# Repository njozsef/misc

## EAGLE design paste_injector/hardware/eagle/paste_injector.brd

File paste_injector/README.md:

Arduino Motorized SMT Solder Paste Dispenser

Original design and code by Zapta
https://github.com/zapta/misc

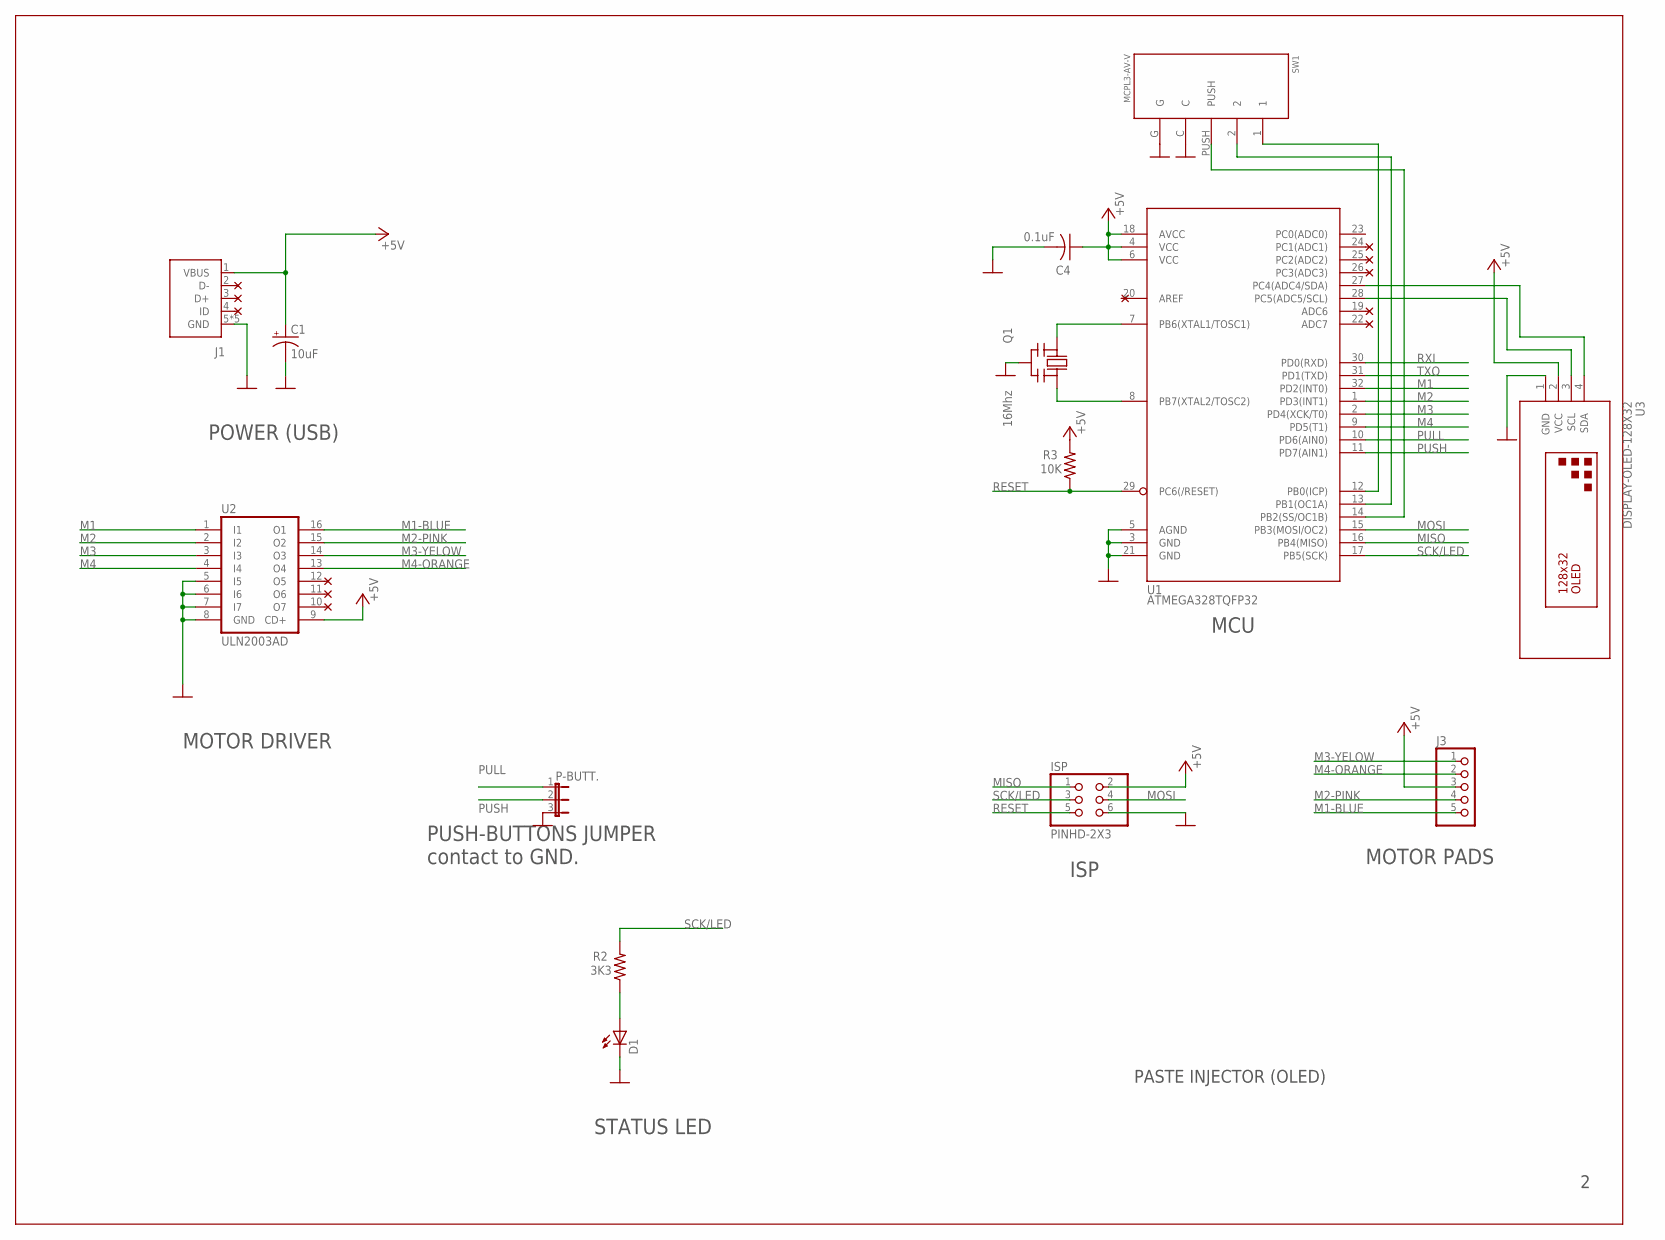
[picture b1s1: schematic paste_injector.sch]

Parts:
C1: 10uF; A/3216-18R
C4: 0.1uF; C0603
D1: LED; LED0603
ISP: PINHD-2X3; 2X03
J1: USB; USB-MICRO-ZX62RD-AB-5P8
J3: PINHD-1X5; 1X05
P-BUTT.: JP2E; JP2
Q1: 16Mhz; CSTCR-G
R2: 3K3; R0603
R3: 10K; R0603
SW1: MCPL3-AV-V; MCPL3-AC-V
U1: ATMEGA328TQFP32; TQFP32-08
U2: ULN2003AD; SO16
U3: DISPLAY-OLED-128X32

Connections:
+5V: C1.+, C4.1, ISP.2, J1.1 (VBUS), J3.3, R3.2, U1.4 (VCC), U1.6 (VCC), U1.18 (AVCC), U2.9 (CD+), U3.2 (VCC)
GND: C1.-, C4.2, D1.C, ISP.6, J1.5 (GND), J1.A (GND), J1.B (GND), J1.C (GND), J1.D (GND), P-BUTT..3, Q1.2 (GND), SW1.C, SW1.G, U1.3 (GND), U1.5 (AGND), U1.21 (GND), U2.5 (I5), U2.6 (I6), U2.7 (I7), U2.8 (GND), U3.1 (GND)
M1: U1.32 (PD2(INT0)), U2.1 (I1)
M1-BLUE: J3.5, U2.16 (O1)
M2: U1.1 (PD3(INT1)), U2.2 (I2)
M2-PINK: J3.4, U2.15 (O2)
M3: U1.2 (PD4(XCK/T0)), U2.3 (I3)
M3-YELOW: J3.1, U2.14 (O3)
M4: U1.9 (PD5(T1)), U2.4 (I4)
M4-ORANGE: J3.2, U2.13 (O4)
MISO: ISP.1, U1.16 (PB4(MISO))
MOSI: ISP.4, U1.15 (PB3(MOSI/OC2))
unnamed: D1.A, R2.1
unnamed: Q1.1 (IN), U1.7 (PB6(XTAL1/TOSC1))
unnamed: U1.27 (PC4(ADC4/SDA)), U3.4 (SDA)
unnamed: U1.28 (PC5(ADC5/SCL)), U3.3 (SCL)
unnamed: SW1.1, U1.12 (PB0(ICP))
unnamed: SW1.2, U1.13 (PB1(OC1A))
unnamed: Q1.3 (OUT), U1.8 (PB7(XTAL2/TOSC2))
unnamed: SW1.PUSH, U1.14 (PB2(SS/OC1B))
PULL: P-BUTT..1, U1.10 (PD6(AIN0))
PUSH: P-BUTT..2, U1.11 (PD7(AIN1))
RESET: ISP.5, R3.1, U1.29 (PC6(/RESET))
RXI: U1.30 (PD0(RXD))
SCK/LED: ISP.3, R2.2, U1.17 (PB5(SCK))
TXO: U1.31 (PD1(TXD))

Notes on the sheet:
PASTE INJECTOR (OLED)
ISP
POWER (USB)
MOTOR DRIVER
MCU
MOTOR PADS
STATUS LED
PUSH-BUTTONS JUMPER contact to GND.

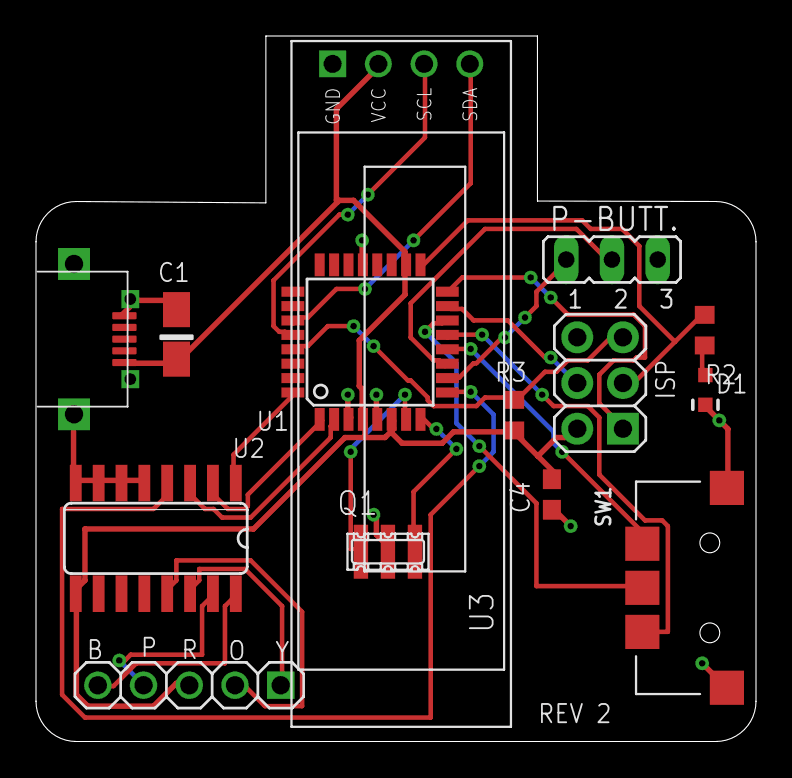
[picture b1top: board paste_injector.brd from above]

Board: 2 copper layers, 40.0 x 39.2 mm, 14 parts (0 on the bottom side), 24 nets.

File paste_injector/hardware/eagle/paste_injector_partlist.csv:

Partlist

Exported from paste_injector.sch at 2018.01.11. 14:08

EAGLE Version 8.5.0 Copyright (c) 1988-2017 Autodesk, Inc.

Assembly variant: 

Part     Value               Device              Package                 Library        Sheet

C1       10uF                CPOL-USA/3216-18R   A/3216-18R              paste_injector 1
C4       0.1uF               CAP-C0603           C0603                   paste_injector 1
D1                           LED                 LED0603                 paste_injector 1
ISP      PINHD-2X3           PINHD-2X3           2X03                    paste_injector 1
J1       USB                 USB                 USB-MICRO-ZX62RD-AB-5P8 paste_injector 1
J3                           PINHD-1X5           1X05                    paste_injector 1
Q1       16Mhz               CERMOSCILL-CSTCRG   CSTCR-G                 adafruit       1
R2       3K3                 RES-R0603           R0603                   paste_injector 1
R3       10K                 RES-R0603           R0603                   paste_injector 1
S1       PUSH_BUTTON         PUSH_BUTTON         PUSH_BUTTON             paste_injector 1
S2       PUSH_BUTTON         PUSH_BUTTON         PUSH_BUTTON             paste_injector 1
SW1      MCPL3-AV-V          MCPL3-AV-V          MCPL3-AC-V              lbrzak         1
U$16     DISPLAY-OLED-128X32 DISPLAY-OLED-128X32 DISPLAY-OLED-128X32     diy-modules    1
U1       ATMEGA328TQFP32     ATMEGA328TQFP32     TQFP32-08               paste_injector 1
U2       ULN2003AD           ULN2003AD           SO16                    paste_injector 1

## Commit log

2018-01-08 forking and first push
2018-01-10 Cleaning other projects
2018-01-11 added oled
2018-01-11 make board

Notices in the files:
parts and their libraries:
diy-modules: Released under the Creative Commons Attribution 4.0 International License: http://creativecommons.org/licenses/by/4.0
